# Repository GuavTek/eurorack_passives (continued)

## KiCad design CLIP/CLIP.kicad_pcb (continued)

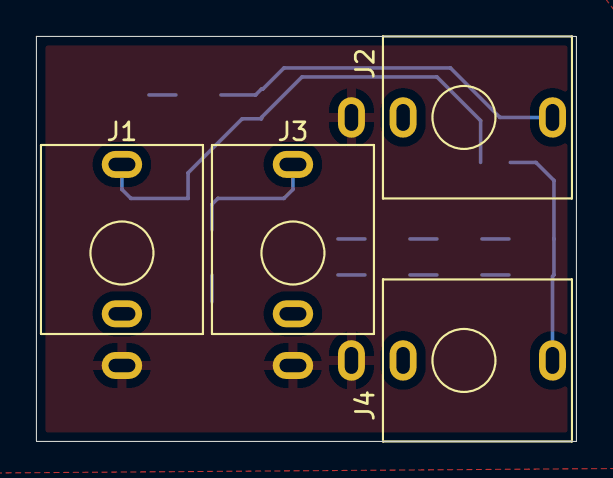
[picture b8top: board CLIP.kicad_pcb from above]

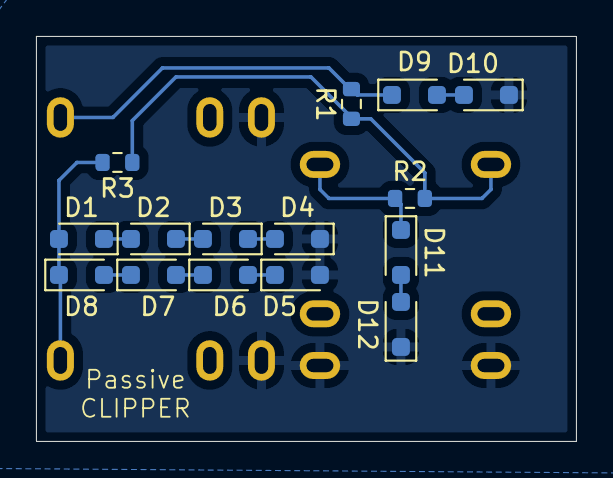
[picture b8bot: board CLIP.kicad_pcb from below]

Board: 2 copper layers, 30.0 x 22.5 mm, 19 parts (15 on the bottom side), 13 nets.

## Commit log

2024-02-21 Add aux output schematic
2024-02-23 Add AND schematic
2024-02-23 Add MULT schematic
2024-02-23 Add OR schematic
2024-02-23 Add RECT schematic
2024-02-23 Add VCA schematic
2024-02-23 Add XOR schematic
2024-03-31 Switch from CC license to CERN open hardware
    CC is apparently not recommended for hardware projects
2024-04-19 Make OR gate lossless
2024-04-20 Increase impedance
2024-04-20 Add patchbay
2024-04-20 Add custom footprints
2024-04-20 Layout aux module
2024-06-16 Add custom footprints and symbols
2024-06-16 Layout XOR
2024-06-16 Layout RECT
2024-06-16 Update to KiCAD8
2024-06-16 Add clipping schematic
2024-06-16 Use relative paths for libraries
2024-06-16 Fix XOR DRC
2024-06-16 Fix rectifier DRC
2024-06-16 Layout patch bay
2024-06-16 Layout OR gate
2024-06-16 Layout mult
2024-06-16 Layout CLIP
2024-06-16 Layout AND gate
2024-06-23 Add AND gate front panel
2024-06-23 Add AUX front panel
2024-06-23 Add CLIPPER front panel
2024-06-23 Add footprint for jack holes
2024-06-23 Add MULT front panel
2024-06-23 Add OR gate front panel
2024-06-23 Add RECT front panel
2024-06-23 Add VCA layout
2024-06-23 Add VCA front panel
2024-06-23 Add XOR gate front panel
2024-06-23 Add PATCH front panel
2024-06-24 Finalize modules
2024-07-21 Improve AND gate off state
2025-04-06 Add pulldown when XOR inputs are high
2025-04-06 Add pulldown when OR inputs are low
2025-04-06 Rename aux_out folder
2025-04-06 Create MULT front panel
